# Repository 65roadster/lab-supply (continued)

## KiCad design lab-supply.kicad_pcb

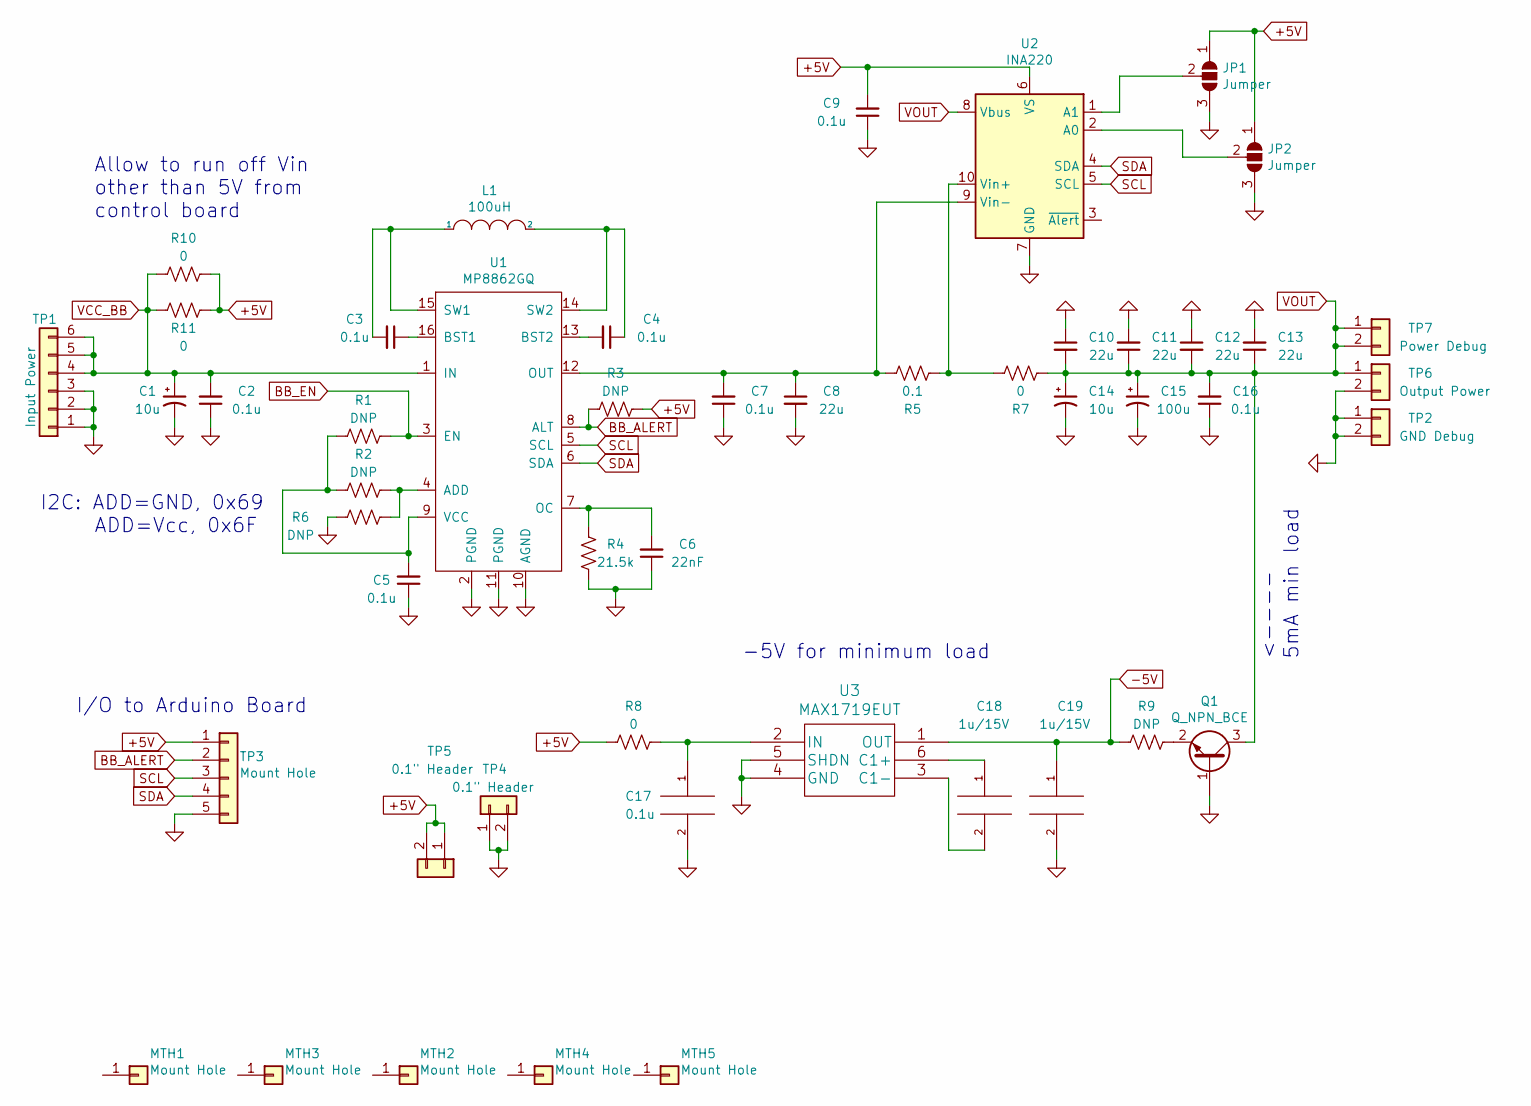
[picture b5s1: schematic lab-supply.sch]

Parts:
C1, C14: 10u; CP_Elec_4x4.5
C2, C3, C4, C5, C7, C9, C16: 0.1u; C_0603_HandSoldering
C6: 22nF; C_0603_HandSoldering
C8, C10, C11, C12, C13: 22u; C_1210_HandSoldering
C15: 100u; CP_Elec_6.3x5.9
C17: 0.1u; C_0805_HandSoldering
C18, C19: 1u/15V; C_0805_HandSoldering
JP1, JP2: Jumper; SolderJumper_3_Pad
L1: 100uH; L_Bourns_SRR1260
MTH1, MTH2, MTH3, MTH4, MTH5: Mount Hole; Mount-Hole-#6
Q1: Q_NPN_BCE; SOT-23
R1, R2, R3, R6, R9: DNP; R_0805_HandSoldering
R4: 21.5k; R_0805_HandSoldering
R5: 0.1; R_2512_HandSoldering
R7, R8, R10, R11: 0; R_0805_HandSoldering
TP1: Input Power; PinHeader_1x06_P2.54mm_Vertical
TP2: GND Debug; PinHeader_1x02_P2.54mm_Vertical
TP3: Mount Hole; JST_XH_B5B-XH-A_1x05_P2.50mm_Vertical
TP4, TP5: 0.1\" Header; PinHeader_1x02_P2.54mm_Vertical
TP6: Output Power; PinHeader_1x02_P2.54mm_Vertical
TP7: Power Debug; PinHeader_1x02_P2.54mm_Vertical
U1: MP8862GQ
U2: INA220; VSSOP-10_3x3mm_P0.5mm
U3: MAX1719EUT; TSOT-23-6_HandSoldering

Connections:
+5V: C9.2, JP1.1 (A), JP2.1 (A), R3.1, R8.2, R10.1, R11.1, TP3.1, TP5.1, TP5.2, U2.6 (VS)
-5V: C19.1, R9.2, U3.1 (OUT)
BB_ALERT: R3.2, TP3.2, U1.8 (ALT)
BB_EN: R1.1, U1.3 (EN)
GND: C1.2, C2.1, C5.1, C6.1, C7.1, C8.2, C9.1, C10.1, C11.2, C12.1, C13.2, C14.2, C15.2, C16.1, C17.2, C19.2, JP1.3 (B), JP2.3 (B), Q1.1 (B), R4.1, R6.2, TP1.1, TP1.2, TP1.3, TP2.2, TP3.5, TP4.1, TP4.2, TP6.1, TP6.2, U1.2 (PGND), U1.10 (AGND), U1.11 (PGND), U2.7 (GND), U3.4 (GND), U3.5 (SHDN)
unnamed: C3.1, U1.16 (BST1)
unnamed: C3.2, L1.1, U1.15 (SW1)
unnamed: C4.1, L1.2, U1.14 (SW2)
unnamed: C4.2, U1.13 (BST2)
unnamed: C5.2, R1.2, R2.2, U1.9 (VCC)
unnamed: C6.2, R4.2, U1.7 (OC)
unnamed: C7.2, C8.1, R5.2, U1.12 (OUT), U2.9 (Vin-)
unnamed: C17.1, R8.1, U3.2 (IN)
unnamed: C18.1, U3.6 (C1+)
unnamed: C18.2, U3.3 (C1-)
unnamed: JP1.2 (C), U2.1 (A1)
unnamed: JP2.2 (C), U2.2 (A0)
unnamed: Q1.2 (E), R9.1
unnamed: R2.1, R6.1, U1.4 (ADD)
unnamed: R5.1, R7.2, U2.10 (Vin+)
SCL: TP3.3, U1.5 (SCL), U2.5 (SCL)
SDA: TP3.4, U1.6 (SDA), U2.4 (SDA)
VCC_BB: C1.1, C2.2, R10.2, R11.2, TP1.4, TP1.5, TP1.6, U1.1 (IN)
VOUT: C10.2, C11.1, C12.2, C13.1, C14.1, C15.1, C16.2, Q1.3 (C), R7.1, TP2.1, TP7.1, TP7.2, U2.8 (Vbus)

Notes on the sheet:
-5V for minimum load
<---- 5mA min load
I/O to Arduino Board
I2C: ADD=GND, 0x69 ADD=Vcc, 0x6F
Allow to run off Vin other than 5V from control board

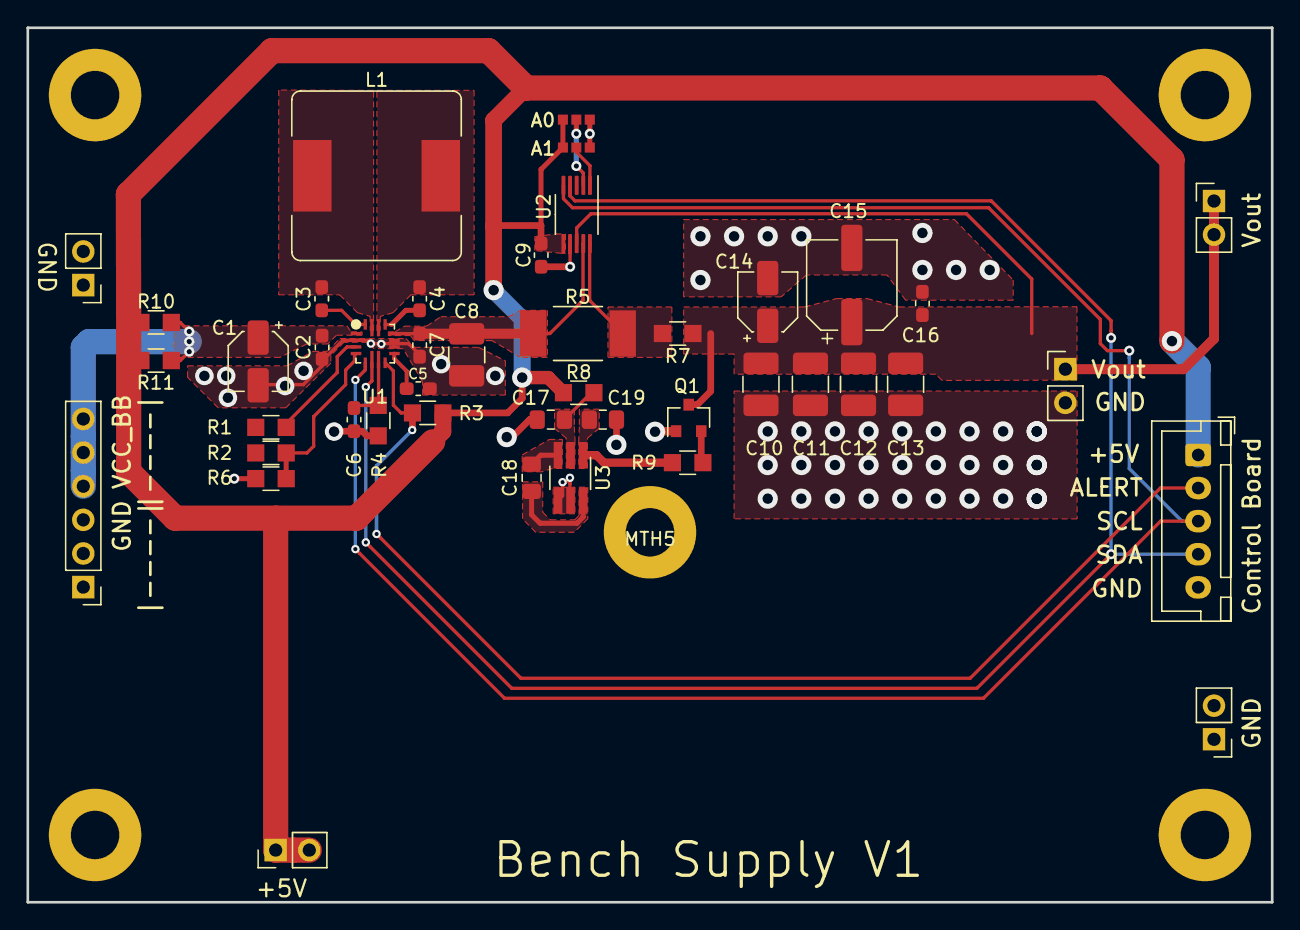
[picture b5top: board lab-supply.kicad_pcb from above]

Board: 2 copper layers, 94.0 x 66.0 mm, 49 parts (0 on the bottom side), 24 nets.

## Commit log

2020-05-27 Kept working on the design
2020-05-28 Updated Control Board
2020-05-28 Added PB0/1 IO Port
2020-05-28 Added FT232
2020-05-30 Worked over the schematic, started layout
2020-05-30 schematic tweak
2020-05-31 Updates to schematic, started control board layout
2020-06-02 Updated control sch, first full cut at layout
2020-06-03 Worked on board layouts
2020-06-04 More work on board layouts
2020-06-05 Separated Vcc_bb from 5V
    Allows for buck/boost to run off of separate Vin from the rest of the circuit. For example +12V
2020-06-10 Lots of updates
2020-06-10 more work
2020-06-11 Next to final edits on control board
2020-06-25 finalized before PCB orders
